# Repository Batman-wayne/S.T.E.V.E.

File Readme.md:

# S.T.E.V.E.

The repository for the Self Teaching Elevated Vehicle Entity. The goal is to make a drone with AI that can interact with a human, capable of avoiding obstacles, recreating its environment, deliver a small payload, and output its telemetry data.

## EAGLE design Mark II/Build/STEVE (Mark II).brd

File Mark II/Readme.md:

# S.T.E.V.E. Mark II

Mark II is the same as Mark I, but replaces the Arduino Uno housing structure with a single PCB. It also excludes the Raspberry Pi 0 and any external peripherals.

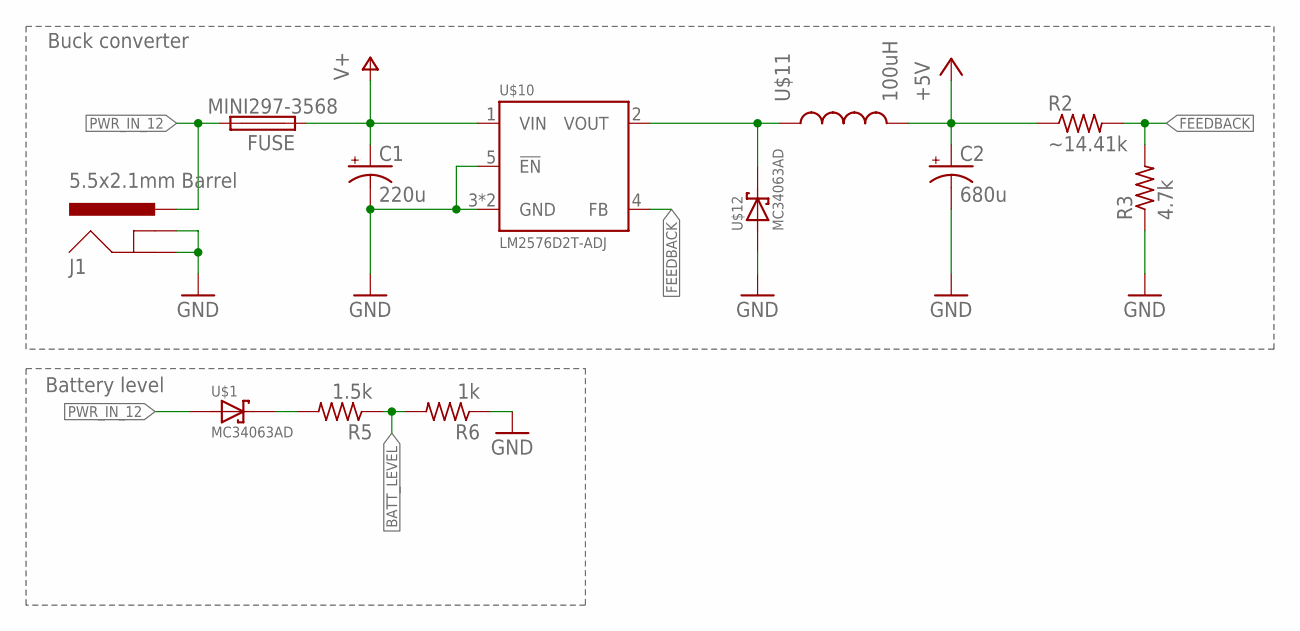
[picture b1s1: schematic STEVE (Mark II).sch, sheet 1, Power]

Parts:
C1: 220u; UD-6,3X7,7_NICHICON
C2: 680u; UD-6,3X7,7_NICHICON
FUSE: MINI297-3568; 3568
J1: 5.5x2.1mm Barrel; POWER_JACK_SMD
R2: ~14.41k; R0603
R3: 4.7k; R0603
R5: 1.5k; R0603
R6: 1k; R0603
U$1, U$12: MC34063AD; SMC
U$10: LM2576D2T-ADJ; TO263-5
U$11: 100uH; 12MM_12MM_INDUCTOR

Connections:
+5V: C2.+, R2.1, U$11.P$2 (2); also elsewhere on the board
BATT_LEVEL: R5.1, R6.2; also elsewhere on the board
FEEDBACK: R2.2, R3.2, U$10.4 (FB)
GND: C1.-, C2.-, J1.GND (GNDBREAK), J1.P$4 (GND), R3.1, R6.1, U$10.3 (GND), U$10.5 (!EN), U$10.6 (GND), U$12.A; also elsewhere on the board
unnamed: R5.2, U$1.C
unnamed: U$10.2 (VOUT), U$11.P$1 (1), U$12.C
PWR_IN_12: FUSE.P$2 (2), FUSE.P$3 (2), J1.VIN0 (PWR)
V+: C1.+, FUSE.P$1 (1), FUSE.P$4 (1), U$10.1 (VIN)

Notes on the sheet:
Buck converter
Battery level

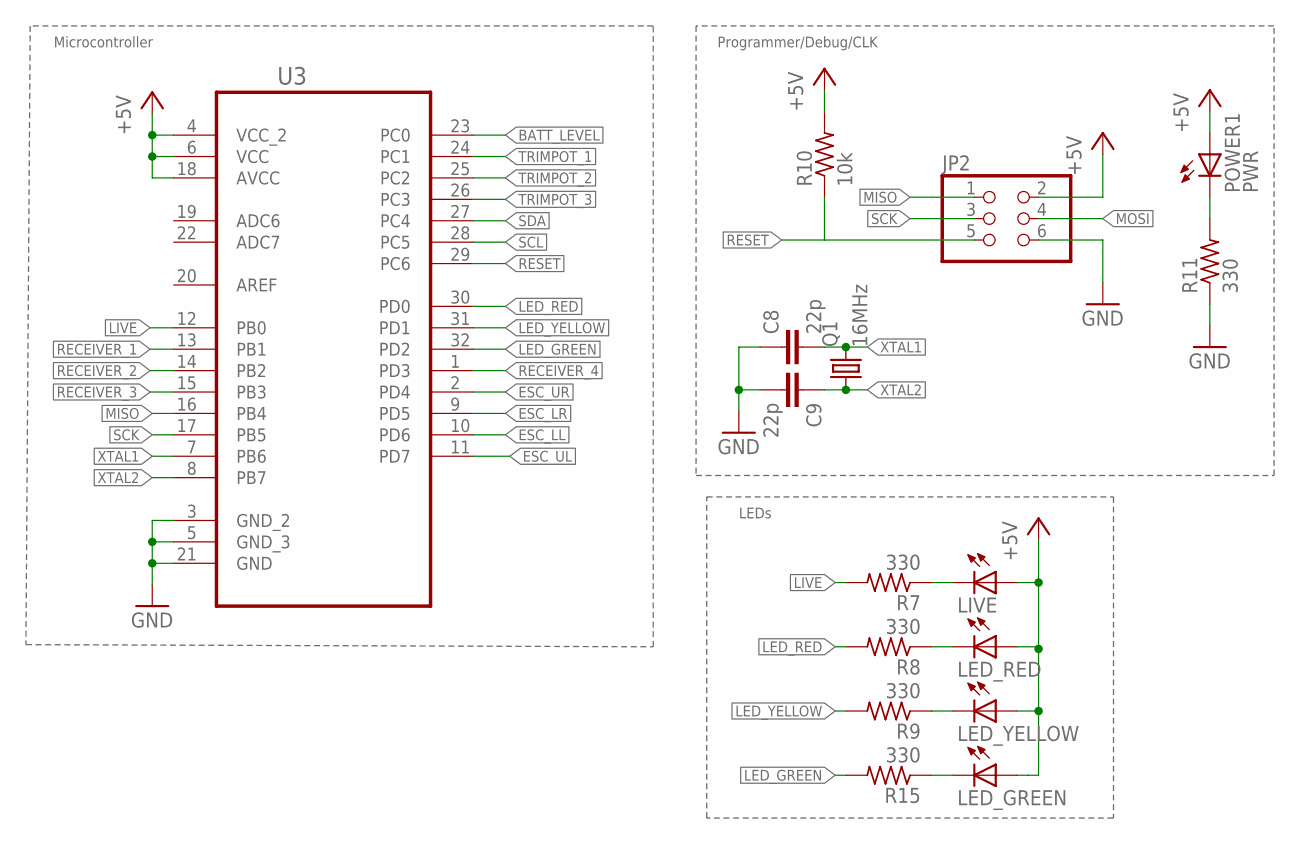
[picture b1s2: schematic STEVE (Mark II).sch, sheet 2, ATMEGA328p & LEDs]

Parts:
C8, C9: 22p; C0805K
JP2: PINHD-2X3; 2X03
LED_GREEN: LEDSML0805; SML0805
LED_RED: LEDSML0805; SML0805
LED_YELLOW: LEDSML0805; SML0805
LIVE: LEDSML0805; SML0805
POWER1: PWR; SML0805
Q1: 16MHz; CTS406
R7, R8, R9, R11, R15: 330; R0805
R10: 10k; R0805
U3: ATMEGA328P-AU; QFP80P900X900X120-32N

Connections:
+5V: JP2.2, LED_GREEN.A, LED_RED.A, LED_YELLOW.A, LIVE.A, POWER1.A, R10.2, U3.4 (VCC_2), U3.6 (VCC), U3.18 (AVCC); also elsewhere on the board
BATT_LEVEL: U3.23 (PC0); also elsewhere on the board
ESC_LL: U3.10 (PD6)
ESC_LR: U3.9 (PD5)
ESC_UL: U3.11 (PD7)
ESC_UR: U3.2 (PD4)
GND: C8.1, C9.2, JP2.6, R11.1, U3.3 (GND_2), U3.5 (GND_3), U3.21 (GND); also elsewhere on the board
LED_GREEN: R15.2, U3.32 (PD2)
LED_RED: R8.2, U3.30 (PD0)
LED_YELLOW: R9.2, U3.31 (PD1)
LIVE: R7.2, U3.12 (PB0)
MISO: JP2.1, U3.16 (PB4)
MOSI: JP2.4
unnamed: POWER1.C, R11.2
unnamed: LIVE.C, R7.1
unnamed: LED_RED.C, R8.1
unnamed: LED_YELLOW.C, R9.1
unnamed: LED_GREEN.C, R15.1
RECEIVER_1: U3.13 (PB1)
RECEIVER_2: U3.14 (PB2)
RECEIVER_3: U3.15 (PB3)
RECEIVER_4: U3.1 (PD3)
RESET: JP2.5, R10.1, U3.29 (PC6)
SCK: JP2.3, U3.17 (PB5)
SCL: U3.28 (PC5); also elsewhere on the board
SDA: U3.27 (PC4); also elsewhere on the board
TRIMPOT_1: U3.24 (PC1); also elsewhere on the board
TRIMPOT_2: U3.25 (PC2); also elsewhere on the board
TRIMPOT_3: U3.26 (PC3); also elsewhere on the board
XTAL1: C8.2, Q1.3 (2), U3.7 (PB6)
XTAL2: C9.1, Q1.1, U3.8 (PB7)

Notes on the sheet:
Microcontroller
Programmer/Debug/CLK
LEDs

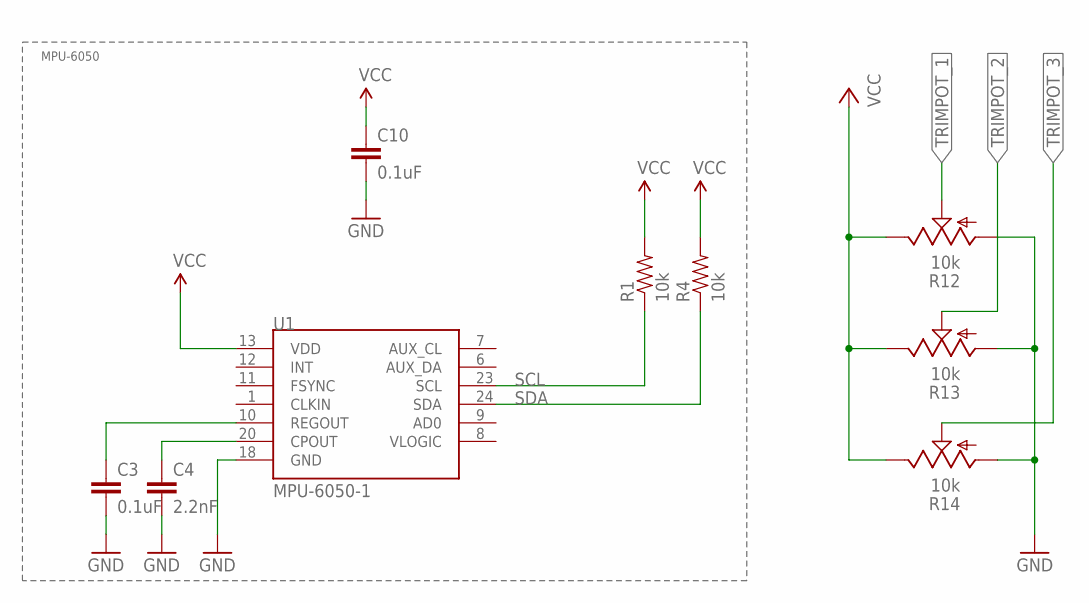
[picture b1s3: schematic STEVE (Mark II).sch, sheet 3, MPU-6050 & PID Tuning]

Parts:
C3, C10: 0.1uF; 0603-CAP
C4: 2.2nF; 0603-CAP
R1, R4: 10k; 0603-RES
R12, R13, R14: 10k; RJ9W
U1: MPU-6050-1; QFN-24-4MM2

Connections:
+5V: R12.E, R13.E, R14.E; also elsewhere on the board
GND: C3.2, C4.2, C10.2, R12.A, R13.A, R14.A, U1.18 (GND); also elsewhere on the board
unnamed: C4.1, U1.20 (CPOUT)
unnamed: C3.1, U1.10 (REGOUT)
SCL: R1.1, U1.23 (SCL); also elsewhere on the board
SDA: R4.1, U1.24 (SDA); also elsewhere on the board
TRIMPOT_1: R12.S; also elsewhere on the board
TRIMPOT_2: R13.S; also elsewhere on the board
TRIMPOT_3: R14.S; also elsewhere on the board
VCC: C10.1, R1.2, R4.2, U1.13 (VDD)

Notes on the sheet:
MPU-6050

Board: 2 copper layers, 37 parts (0 on the bottom side), 30 nets, no tracks yet.

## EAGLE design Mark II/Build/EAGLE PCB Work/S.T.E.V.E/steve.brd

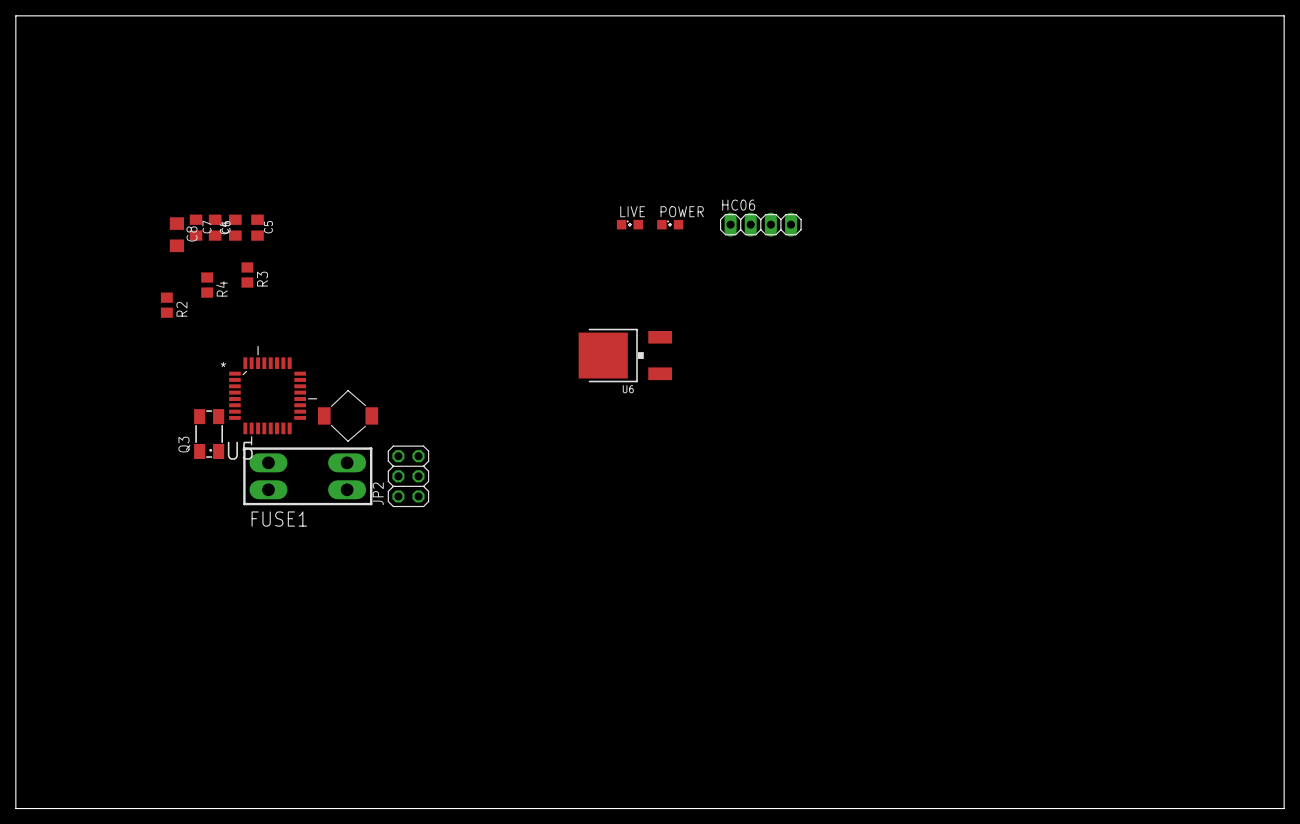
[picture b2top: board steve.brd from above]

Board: 2 copper layers, 160.0 x 100.0 mm, 17 parts (0 on the bottom side), 15 nets, no tracks yet.

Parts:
C4, C5: 22p; C0805K
C6: 0.1u; C0805K
C7: 0.22u; C0805K
C8: 220u; C1206
FUSE1: MINI297-3568; 3568
HC06: 1X04
JP2: 2X03
L2: 20uH; MSS7348
LIVE: LIVE; SML0805
POWER: PWR; SML0805
Q3: 16MHz; CTS406
R2: 10k; R0805
R3, R4: 330; R0805
U5: QFP80P900X900X120-32N
U6: MC7805BDD; DPAK

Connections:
+5V: C6.1, HC06.1, JP2.2, LIVE.A, POWER.A, R2.2, U5.4, U5.6, U5.18, U6.2
+12V: C7.1, C8.1, L2.P$2, U6.1
GND: C4.1, C5.2, C6.2, C7.2, C8.2, HC06.2, JP2.6, R3.1, U5.3, U5.5, U5.21, U6.3
LIVE: R4.1, U5.11
MISO: JP2.1, U5.16
MOSI: JP2.4, U5.15
unnamed: POWER.C, R3.2
unnamed: LIVE.C, R4.2
PWR_IN: FUSE1.P$1, FUSE1.P$2, FUSE1.P$3, FUSE1.P$4, L2.P$1
RESET: JP2.5, R2.1, U5.29
RX: HC06.4, U5.31
SCK: JP2.3, U5.17
TX: HC06.3, U5.30
XTAL1: C4.2, Q3.3, U5.7
XTAL2: C5.1, Q3.1, U5.8

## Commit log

2018-08-16 Commits done
2018-08-16 Moved directories
2018-08-16 Reorganized
2018-08-16 ahsd
2018-08-16 Renames
2018-08-16 Mark II redone
2018-08-17 Repo Readme updated
2018-08-18 Began Mark II schematic
2018-08-19 Mark II schematic finished, board in progress
2018-08-19 Mark II board in progress
2019-01-02 Added gitignore to prevent mass amounts of weird file names
2019-01-02 Removed the Mark II build as an experiment
2019-01-02 Adding the old build files

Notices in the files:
parts and their libraries:
SparkFun-Connectors: Licensing: Creative Commons ShareAlike 4.0 International - https://creativecommons.org/licenses/by-sa/4.0
